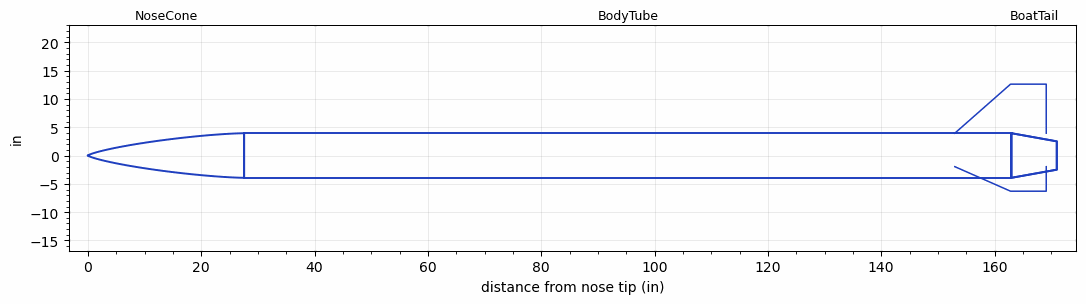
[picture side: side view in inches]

<RASAeroDocument>
 <FileVersion>2</FileVersion>
 <RocketDesign>
  <NoseCone>
   <Length>27.56</Length>
   <Diameter>7.87</Diameter>
   <Shape>Von Karman Ogive</Shape>
   <Location>0</Location>
  </NoseCone>
  <BodyTube>
   <Length>135.43</Length>
   <Diameter>7.87</Diameter>
   <Location>27.56</Location>
   <BoattailLength>8</BoattailLength>
   <BoattailRearDiameter>5</BoattailRearDiameter>
   <Overhang>6.146999</Overhang>
   <Fin>
    <Count>3</Count>
    <Chord>16.147</Chord>
    <Span>8.66</Span>
    <SweepDistance>9.84</SweepDistance>
    <TipChord>6.3</TipChord>
    <Thickness>0.118</Thickness>
    <Location>10</Location>
    <AirfoilSection>Hexagonal</AirfoilSection>
    <FX1>1</FX1>
    <FX3>1</FX3>
   </Fin>
   <Protuberance>
    <StreamlinedNoBaseDrag>0.62</StreamlinedNoBaseDrag>
    <StreamlinedWithBaseDrag>0</StreamlinedWithBaseDrag>
    <InclinedPlate1Angle>0</InclinedPlate1Angle>
    <InclinedPlate1FrontalArea>0</InclinedPlate1FrontalArea>
    <InclinedPlate2Angle>0</InclinedPlate2Angle>
    <InclinedPlate2FrontalArea>0</InclinedPlate2FrontalArea>
   </Protuberance>
  </BodyTube>
  <BoatTail>
   <Length>8</Length>
   <Diameter>7.87</Diameter>
   <RearDiameter>5</RearDiameter>
   <Location>162.99</Location>
  </BoatTail>
  <Surface>Smooth Paint</Surface>
  <ModifiedBarrowman>False</ModifiedBarrowman>
  <Turbulence>False</Turbulence>
  <UseBooster1>False</UseBooster1>
  <UseBooster2>False</UseBooster2>
 </RocketDesign>
 <LaunchSite>
  <Altitude>0</Altitude>
  <Pressure>0</Pressure>
  <RodAngle>6</RodAngle>
  <RodLength>39</RodLength>
  <Temperature>74</Temperature>
  <WindSpeed>9.46</WindSpeed>
 </LaunchSite>
 <Recovery>
  <Altitude1>1000</Altitude1>
  <Altitude2>1000</Altitude2>
  <DeviceType1>None</DeviceType1>
  <DeviceType2>None</DeviceType2>
  <Event1>False</Event1>
  <Event2>False</Event2>
  <Size1>1</Size1>
  <Size2>1</Size2>
  <EventType1>None</EventType1>
  <EventType2>None</EventType2>
  <CD1>1.33</CD1>
  <CD2>1.33</CD2>
 </Recovery>
 <SimulationList>
  <Simulation>
   <SustainerEngine>RL1  (ICLR)</SustainerEngine>
   <SustainerLaunchWt>173.56</SustainerLaunchWt>
   <SustainerNozzleDiameter>3</SustainerNozzleDiameter>
   <SustainerCG>103.54</SustainerCG>
   <SustainerIgnitionDelay>0</SustainerIgnitionDelay>
   <Booster1SeparationDelay>0</Booster1SeparationDelay>
   <Booster1IgnitionDelay>0</Booster1IgnitionDelay>
   <IncludeBooster1>False</IncludeBooster1>
   <Booster2Delay>0</Booster2Delay>
   <IncludeBooster2>False</IncludeBooster2>
   <TimetoApogee>38.60953</TimetoApogee>
   <MaxAltitude>23804.78</MaxAltitude>
   <MaxVelocity>1474.345</MaxVelocity>
  </Simulation>
 </SimulationList>
</RASAeroDocument>
